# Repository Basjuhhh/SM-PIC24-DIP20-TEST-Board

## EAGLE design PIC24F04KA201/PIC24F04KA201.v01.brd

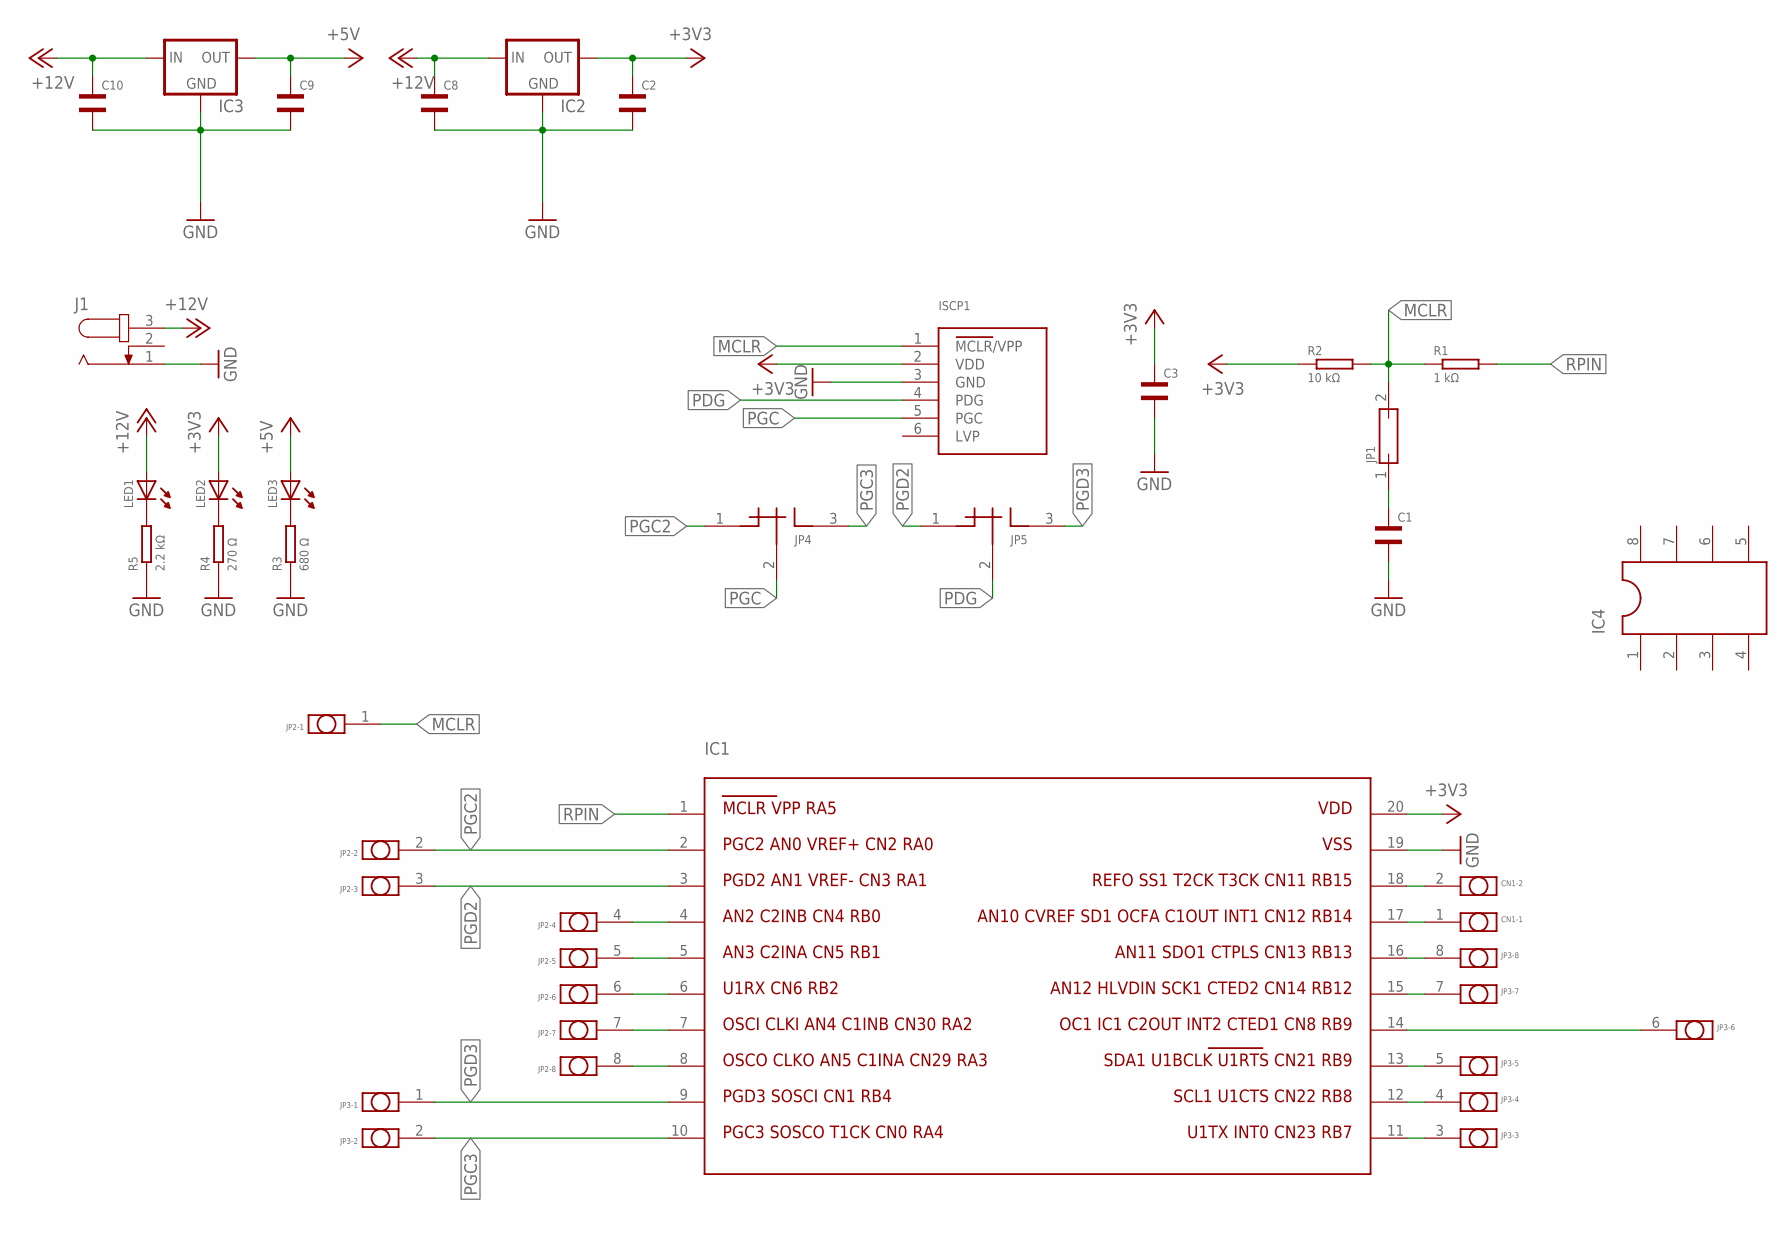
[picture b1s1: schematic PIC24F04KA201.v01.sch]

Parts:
C1, C2, C3, C8, C9, C10: CAP-SMD-0805; SMD-0805
CN1: 1X2
IC1: PIC24F04KA201; DIP-20-SOCKET
IC2: LD1117V33; TO-220-STANDING
IC3: L78S05CV; TO-220-STANDING
IC4: DIP-08S; DIP-08-SOCKET
ISCP1: ICSP1X6-2.54; 1X6-2.54
J1: JACK-PLUG0; SPC4077
JP1: JP; 1X2
JP2, JP3: 1X8
JP4, JP5: JP-OR; 1X3
LED1, LED2, LED3: LED-SMD-0805; SMD-0805
R1: 1 kΩ; SMD-2012(0805)
R2: 10 kΩ; SMD-2012(0805)
R3: 680 Ω; SMD-2012(0805)
R4: 270 Ω; SMD-2012(0805)
R5: 2.2 kΩ; SMD-2012(0805)

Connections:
+3V3: C2.2, C3.2, IC1.20, IC2.2 (OUT), ISCP1.2 (VDD), LED2.A, R2.1
+5V: C9.2, IC3.3 (OUT), LED3.A
+12V: C8.2, C10.2, IC2.3 (IN), IC3.1 (IN), J1.3, LED1.A
GND: C1.1, C2.1, C3.1, C8.1, C9.1, C10.1, IC1.19, IC2.1 (GND), IC3.2 (GND), ISCP1.3 (GND), J1.1, R3.1, R4.1, R5.1
MCLR: ISCP1.1 (MCLR/VPP), JP1.2, JP2.1, R1.1, R2.2
unnamed: C1.2, JP1.1
unnamed: IC1.4, JP2.4
unnamed: LED3.C, R3.2
unnamed: LED2.C, R4.2
unnamed: LED1.C, R5.2
unnamed: IC1.6, JP2.6
unnamed: IC1.5, JP2.5
unnamed: IC1.7, JP2.7
unnamed: IC1.8, JP2.8
unnamed: IC1.16, JP3.8
unnamed: IC1.15, JP3.7
unnamed: IC1.14, JP3.6
unnamed: IC1.13, JP3.5
unnamed: IC1.12, JP3.4
unnamed: IC1.11, JP3.3
unnamed: CN1.1, IC1.17
unnamed: CN1.2, IC1.18
PDG: ISCP1.4 (PDG), JP5.2
PGC: ISCP1.5 (PGC), JP4.2
PGC2: IC1.2, JP2.2, JP4.1
PGC3: IC1.10, JP3.2, JP4.3
PGD2: IC1.3, JP2.3, JP5.1
PGD3: IC1.9, JP3.1, JP5.3
RPIN: IC1.1, R1.2

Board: 2 copper layers, 26 parts (0 on the bottom side), 29 nets, no tracks yet.

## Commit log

2014-06-27 SM-PIC24-DIP20-TEST-Board
    Initial stage
2014-06-27 Update - added jumpers & Vreg's
2014-06-27 .gitignore
    #################
    ## EAGLE
    #################
    *.s#?
    *.b#?
    *.l#?
2014-06-27 ignore
2014-06-27 Revert ".gitignore"
    This reverts commit d6c0fbecffe5c17840d2024fe027295ae43c87ec.
2014-06-27 Revert "Revert ".gitignore""
    This reverts commit 8627ea6dd9aa78824a0229700a801680ca33d9f7.
2014-06-27 Revert "Revert "Revert ".gitignore"""
    This reverts commit 8858f0831dc9f5f8860333548b6fe65309b4e6b0.
2014-06-27 Revert "Revert "Revert "Revert ".gitignore""""
    This reverts commit bc4214116bfcbcf59c972c7a9f3607f949689ca2.
2014-06-27 Small parts update
2014-06-27 Added correct values for resistors, resynced the board file
2014-06-28 Added dip8
